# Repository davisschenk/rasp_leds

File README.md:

# WS281x Raspberry PI Led Controller
This project was meant as a way for me to learn a little bit about electroics and pcb design, aswell as to be an outlet to learn rust and mess around with building a frontend for a larger project. This is very much still a WIP and I will be continuing to work on this project in my sparetime. I will do my best to document how things work and do small writeups explaining the project, if you are interested I highly encourage looking through the repository because I have readme's for each main section of this project (backend, frontend, hardware). Eventually I may document setup if anyone else is intrested in replicating this, but for now im still working on improving pretty much everything.

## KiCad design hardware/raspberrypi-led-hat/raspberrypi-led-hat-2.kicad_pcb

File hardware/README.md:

# Hardware
I used a Raspberry PI 3 B+ with a custom PCB mounted on top that handles signal level conversion and the connection with the leds through a custom made wire. Below is a parts list with everything I used, and all the files for the custom pcb I designed using kicad are also in this directory. I chose to switch to using a 4 pin connector in case I ever decide that I would like to use WS2815 leds instead of W2812b due to the fact that the WS2812b's suffer from lots of voltage drop.

## Parts used
* Raspberry PI 3 B+
* 3.3v -> 5v Logic Level Converter ([BOB-12009](https://www.digikey.com/en/products/detail/sparkfun-electronics/BOB-12009/5673795?s=N4IgTCBcDaIEIHk4FoCMYAMGCcIC6AvkA))
* WS2812b LED light strip
* [5v Barrel Powerjack](https://www.digikey.com/en/products/detail/cui-devices/PJ-063AH/2161208)
* Micro-Fit 3.0 Molex Connectors
    * [Header connector](https://www.digikey.com/en/products/detail/molex/0430450400/252527?s=N4IgTCBcDaIOoFkCMAOJAWAtAOQCIgF0BfIA)
    * [Cable Assembly](https://www.digikey.com/en/products/detail/molex/0451320401/6208003?s=N4IgTCBcDaIAQMQg6gWQIwDZ1YLQDkAREAXQF8g)
* 03/18 Solid Core Thermostat Cable
* 5v power supply
* [Custom designed pcb](raspberrypi-led-hat)

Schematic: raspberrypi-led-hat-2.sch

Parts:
J1: Barrel_Jack; BarrelJack_CUI_PJ-063AH_Horizontal
J2: Conn_02x02_Counter_Clockwise; 430450400
MK1, MK2, MK3, MK4: M2.5; MountingHole_2.7mm_M2.5
P1: Conn_02x20_Odd_Even; PinSocket_2x20_P2.54mm_Vertical
R1: R; R_Axial_DIN0204_L3.6mm_D1.6mm_P2.54mm_Vertical
SW1: SW_Push; SW_PUSH_6mm
U1: BOB-12009; CONV_BOB-12009; PARTREV 01

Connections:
+3V3: P1.1, P1.17, SW1.1, U1.LV
+5V: J1.1, J2.1, U1.HV
/GPIO2(SDA1): P1.3
/GPIO3(SCL1): P1.5
/GPIO4(GCLK): P1.7
/GPIO5: P1.29
/GPIO6: P1.31
/GPIO7(SPI1_CE_N): P1.26
/GPIO8(SPI0_CE_N): P1.24
/GPIO9(SPI0_MISO): P1.21
/GPIO10(SPI0_MOSI): P1.19
/GPIO11(SPI0_SCK): P1.23
/GPIO12(PWM0): P1.32
/GPIO13(PWM1): P1.33
/GPIO14(TXD0): P1.8
/GPIO15(RXD0): P1.10, R1.2
/GPIO16: P1.36
/GPIO17(GEN0): P1.11
/GPIO18(GEN1)(PWM0): P1.12, U1.LV1
/GPIO19(SPI1_MISO): P1.35
/GPIO20(SPI1_MOSI): P1.38
/GPIO21(SPI1_SCK): P1.40
/GPIO22(GEN3): P1.15
/GPIO23(GEN4): P1.16
/GPIO24(GEN5): P1.18
/GPIO25(GEN6): P1.22
/GPIO26: P1.37
/GPIO27(GEN2): P1.13
/ID_SC: P1.28
/ID_SD: P1.27
/LED_DATA: J2.3, J2.4, U1.HV1
GND: J1.2, J2.2, P1.6, P1.9, P1.14, P1.20, P1.25, P1.30, P1.34, P1.39, U1.GND_1 (GND), U1.GND_2 (GND)
unnamed: P1.2, P1.4
unnamed: R1.1, SW1.2

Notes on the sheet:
ID_SD and ID_SC PINS: These pins are reserved for HAT ID EEPROM. At boot time this I2C interface will be interrogated to look for an EEPROM that identifes the attached board and allows automagic setup of the GPIOs (and optionally, Linux drivers). DO NOT USE these pins for anything other than attach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
Mounting Holes

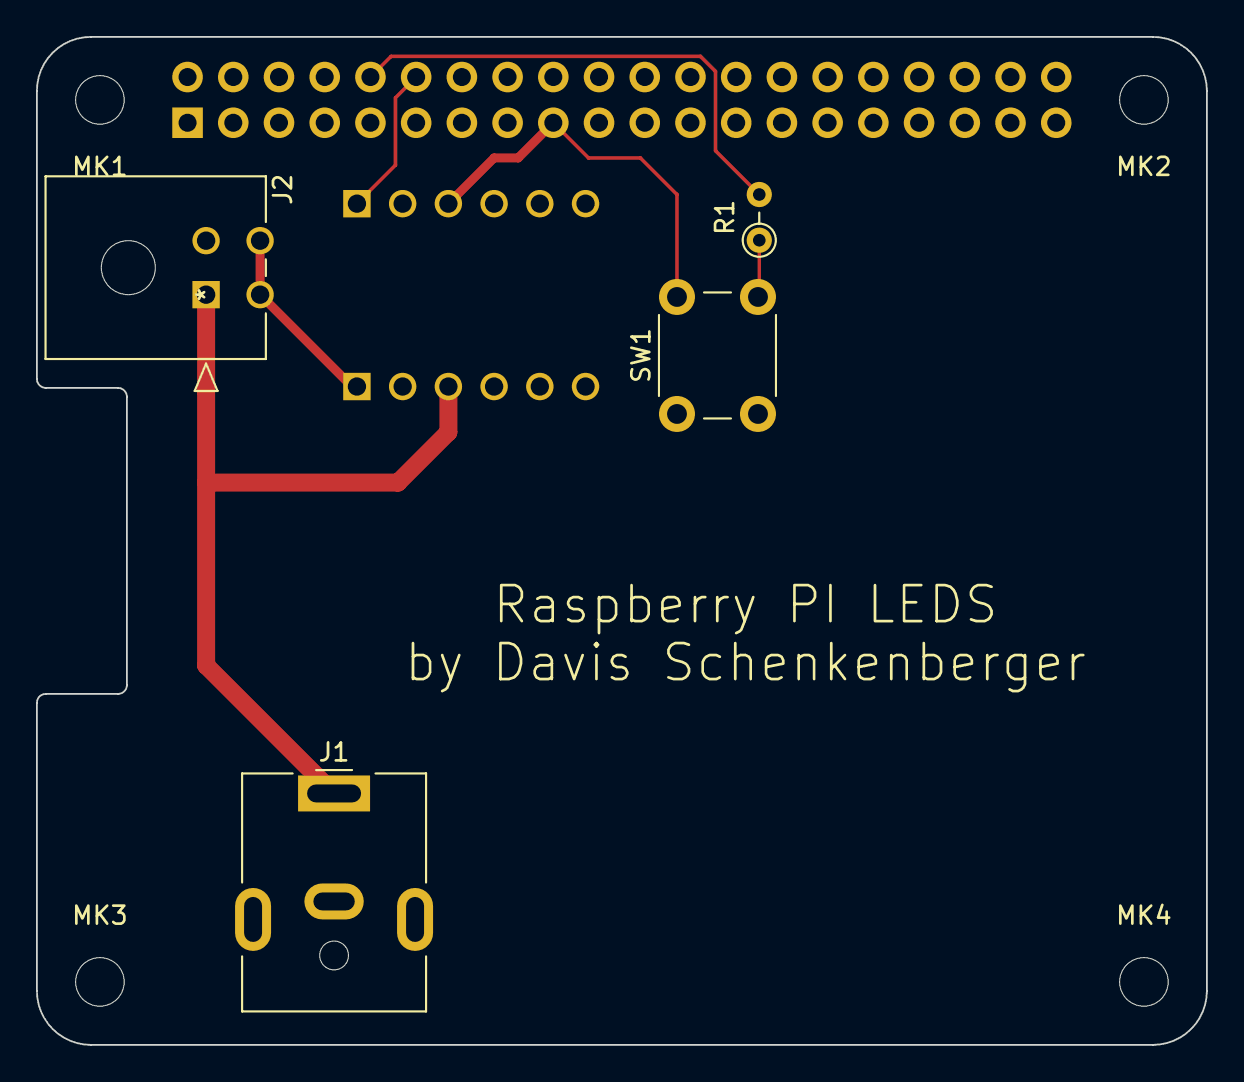
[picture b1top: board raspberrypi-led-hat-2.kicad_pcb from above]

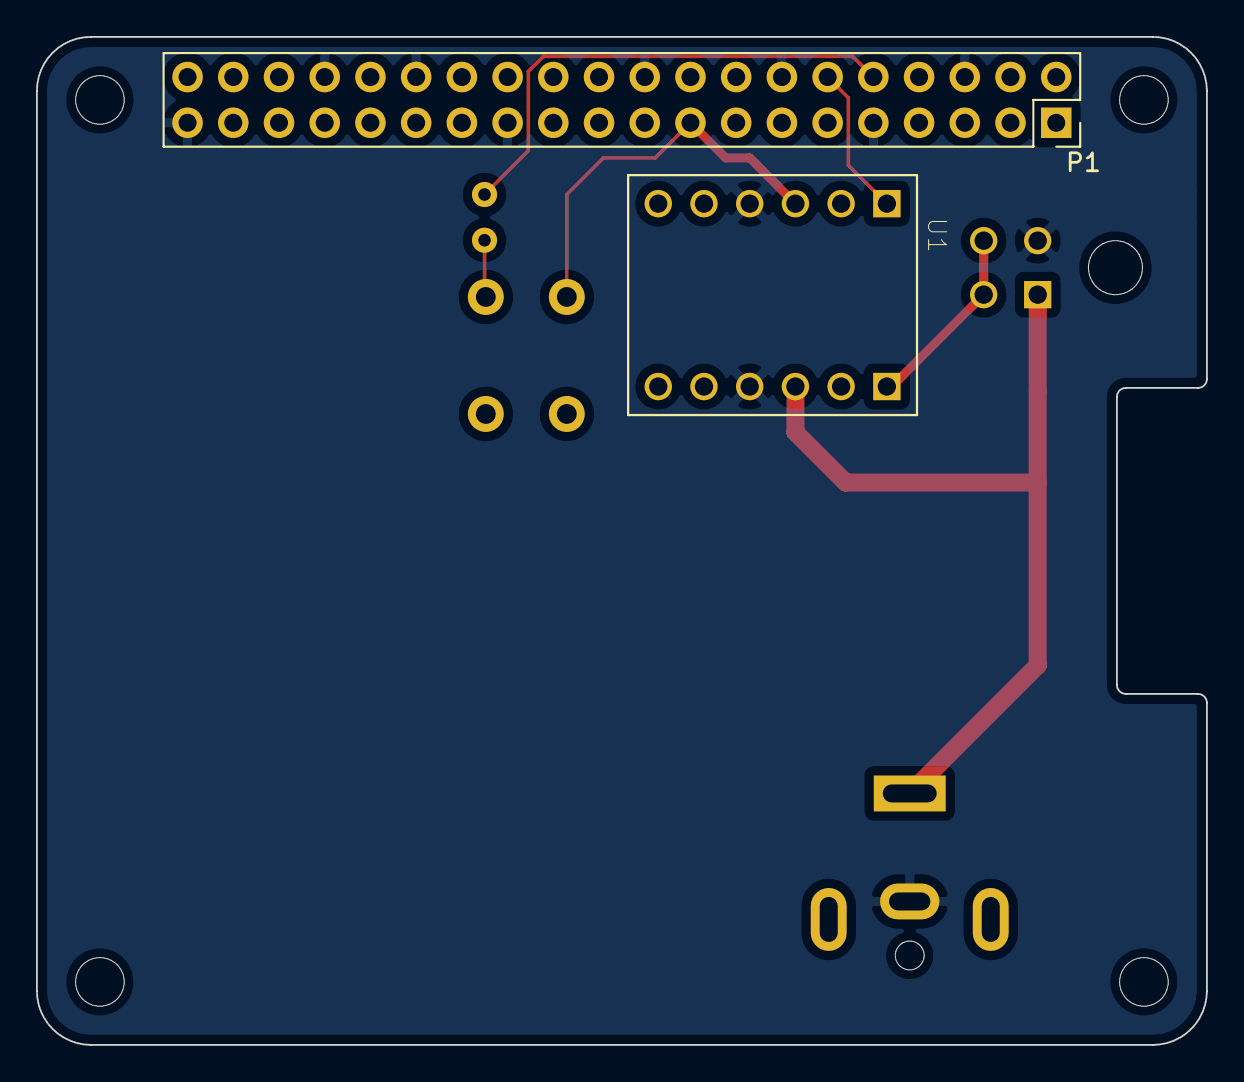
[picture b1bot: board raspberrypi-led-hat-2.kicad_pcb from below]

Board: 2 copper layers, 65.0 x 56.0 mm, 10 parts (2 on the bottom side), 8 nets.

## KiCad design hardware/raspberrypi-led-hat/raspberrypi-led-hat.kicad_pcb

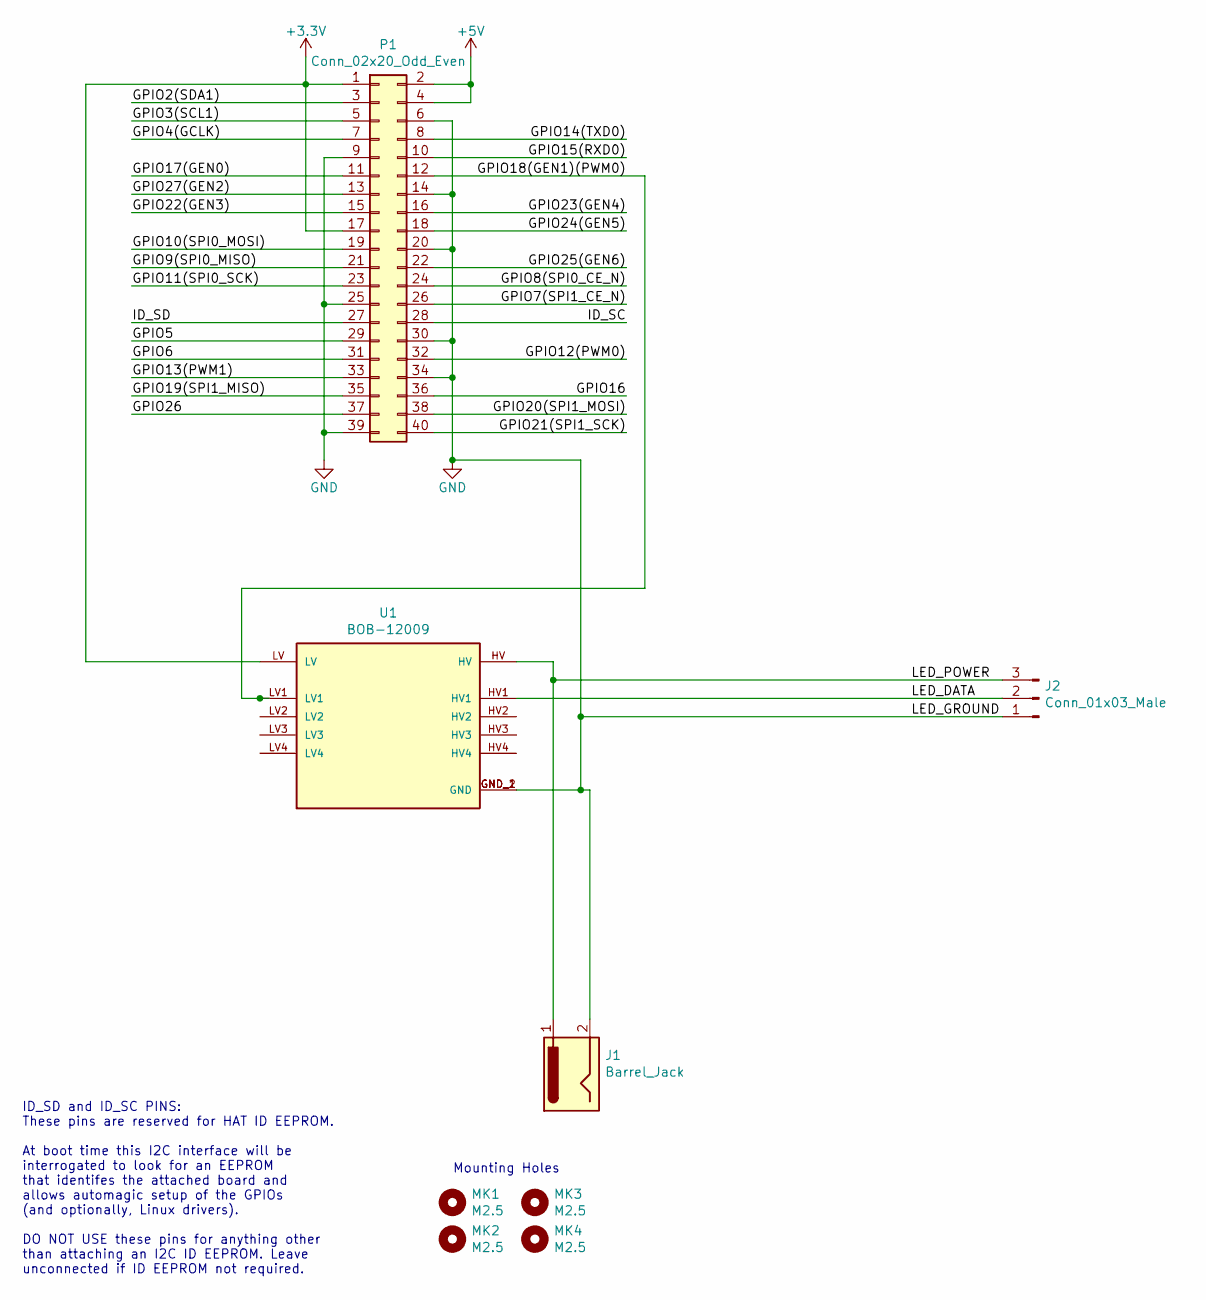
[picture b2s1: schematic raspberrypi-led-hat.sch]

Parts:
J1: Barrel_Jack; BarrelJack_CUI_PJ-063AH_Horizontal
J2: Conn_01x03_Male; Molex-0901362203
MK1, MK2, MK3, MK4: M2.5; MountingHole_2.7mm_M2.5
P1: Conn_02x20_Odd_Even; PinSocket_2x20_P2.54mm_Vertical
U1: BOB-12009; CONV_BOB-12009; PARTREV 01

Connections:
+3V3: P1.1, P1.17, U1.LV
+5V: P1.2, P1.4
/GPIO2(SDA1): P1.3
/GPIO3(SCL1): P1.5
/GPIO4(GCLK): P1.7
/GPIO5: P1.29
/GPIO6: P1.31
/GPIO7(SPI1_CE_N): P1.26
/GPIO8(SPI0_CE_N): P1.24
/GPIO9(SPI0_MISO): P1.21
/GPIO10(SPI0_MOSI): P1.19
/GPIO11(SPI0_SCK): P1.23
/GPIO12(PWM0): P1.32
/GPIO13(PWM1): P1.33
/GPIO14(TXD0): P1.8
/GPIO15(RXD0): P1.10
/GPIO16: P1.36
/GPIO17(GEN0): P1.11
/GPIO18(GEN1)(PWM0): P1.12, U1.LV1
/GPIO19(SPI1_MISO): P1.35
/GPIO20(SPI1_MOSI): P1.38
/GPIO21(SPI1_SCK): P1.40
/GPIO22(GEN3): P1.15
/GPIO23(GEN4): P1.16
/GPIO24(GEN5): P1.18
/GPIO25(GEN6): P1.22
/GPIO26: P1.37
/GPIO27(GEN2): P1.13
/ID_SC: P1.28
/ID_SD: P1.27
/LED_DATA: J2.2, U1.HV1
/LED_POWER: J1.1, J2.3, U1.HV
GND: J1.2, J2.1, P1.6, P1.9, P1.14, P1.20, P1.25, P1.30, P1.34, P1.39, U1.GND_1 (GND), U1.GND_2 (GND)

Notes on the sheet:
ID_SD and ID_SC PINS: These pins are reserved for HAT ID EEPROM. At boot time this I2C interface will be interrogated to look for an EEPROM that identifes the attached board and allows automagic setup of the GPIOs (and optionally, Linux drivers). DO NOT USE these pins for anything other than attach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
Mounting Holes

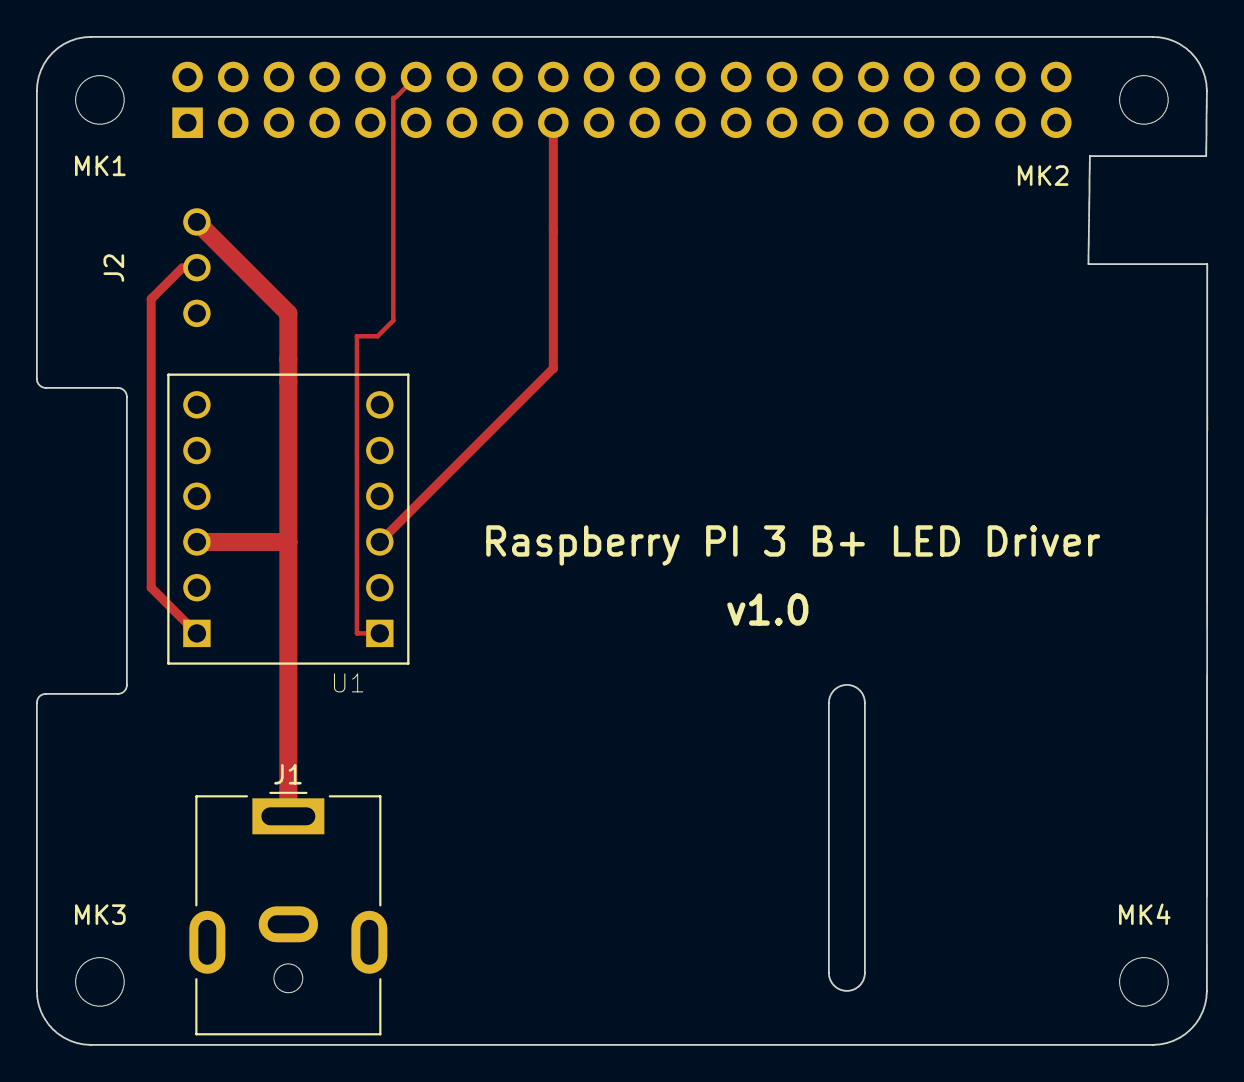
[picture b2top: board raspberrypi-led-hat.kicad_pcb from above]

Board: 2 copper layers, 65.0 x 56.0 mm, 8 parts (1 on the bottom side), 6 nets.

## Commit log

2021-06-07 Added schematic for LED Raspberry PI hat
2021-06-07 Added state diagram
2021-06-07 Added a readme for the backend
2021-06-07 Fixed alt text in readme
2021-06-07 Uncommented gunk in build script
2021-06-07 Added more files for schematic
2021-06-07 fixed build script again
2021-06-07 Updated build command to use flag to control building web page
2021-06-09 Added assets
2021-06-09 Added github workflow to autobuild docs
2021-06-09 Added some comments and replaced hard coded values
2021-06-09 Remade hat kicad and added readme
2021-06-09 Updated rustdoc.yaml
2021-06-12 Run cargo fmt
2021-06-12 Added RenderOnce tick action to avoid boiler plate in static patterns
2021-06-12 Converted some for loops through mut iter to for eachs
2021-06-16 Switched from react to flutter
2021-06-16 Abstracted Message/pattern behavior
2021-09-30 added pattern and power mode
2021-09-30 deploy: 995f0b9be27ba9fbfb23e57bbd64462cc8540cf8

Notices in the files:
parts and their libraries:
Copyright 2021 Accelerated Designs. All rights reserved.
